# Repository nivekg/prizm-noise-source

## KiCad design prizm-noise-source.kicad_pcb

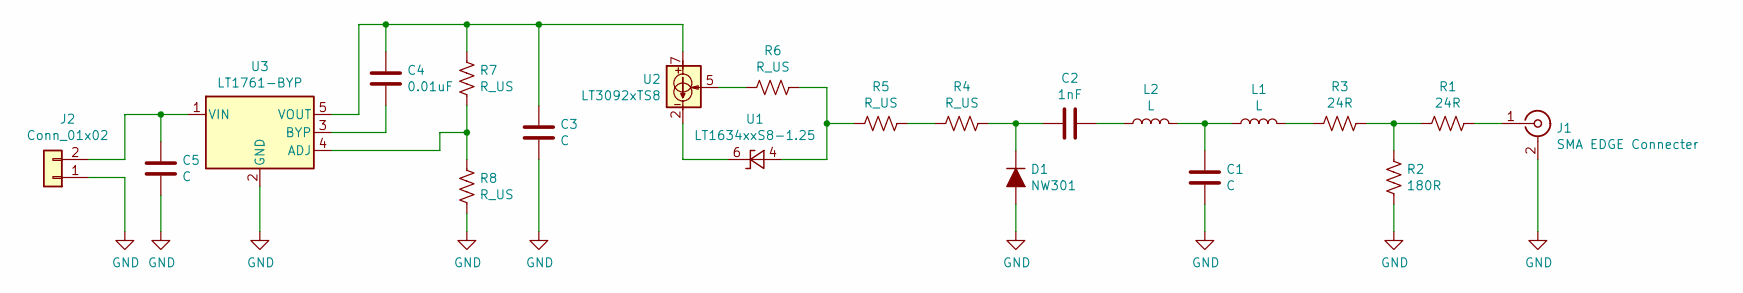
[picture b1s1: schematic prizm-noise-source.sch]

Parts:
C1, C3, C5: C; C_0603_1608Metric
C2: 1nF; C_0603_1608Metric
C4: 0.01uF; C_0603_1608Metric
D1: NW301; D_SOD-323
J1: SMA EDGE Connecter; SMA_Amphenol_132289_EdgeMount
J2: Conn_01x02; PinHeader_1x02_P2.54mm_Vertical
L1, L2: L; L_0603_1608Metric
R1, R3: 24R; R_0603_1608Metric
R2: 180R; R_0603_1608Metric
R4, R5, R6, R7, R8: R_US; R_0603_1608Metric
U1: LT1634xxS8-1.25; SO-8_3.9x4.9mm_P1.27mm
U2: LT3092xTS8; TSOT-23-8
U3: LT1761-BYP; TSOT-23-5

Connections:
GND: C1.2, C3.2, C5.2, D1.2 (A), J1.2 (Ext), J2.1, R2.2, R8.2, U3.2 (GND)
unnamed: C1.1, L1.1, L2.2
unnamed: C2.1, L2.1
unnamed: C2.2, D1.1 (K), R4.1
unnamed: C3.1, C4.1, R7.1, U2.7, U2.8, U3.5 (VOUT)
unnamed: C4.2, U3.3 (BYP)
unnamed: C5.1, J2.2, U3.1 (VIN)
unnamed: J1.1 (In), R1.2
unnamed: L1.2, R3.2
unnamed: R1.1, R2.1, R3.1
unnamed: R4.2, R5.1
unnamed: R5.2, R6.1, U1.4 (A)
unnamed: R6.2, U2.5
unnamed: R7.2, R8.1, U3.4 (ADJ)
unnamed: U1.6 (K), U2.2, U2.3, U2.4

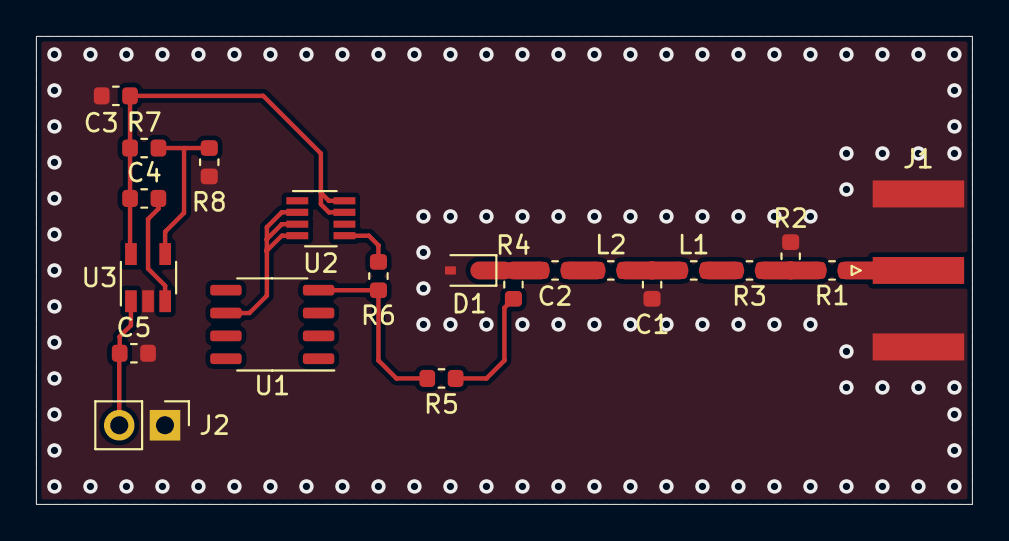
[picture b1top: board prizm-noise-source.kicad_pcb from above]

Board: 2 copper layers, 52.0 x 26.0 mm, 21 parts (0 on the bottom side), 15 nets.

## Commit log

2019-06-18 partial noise source design
